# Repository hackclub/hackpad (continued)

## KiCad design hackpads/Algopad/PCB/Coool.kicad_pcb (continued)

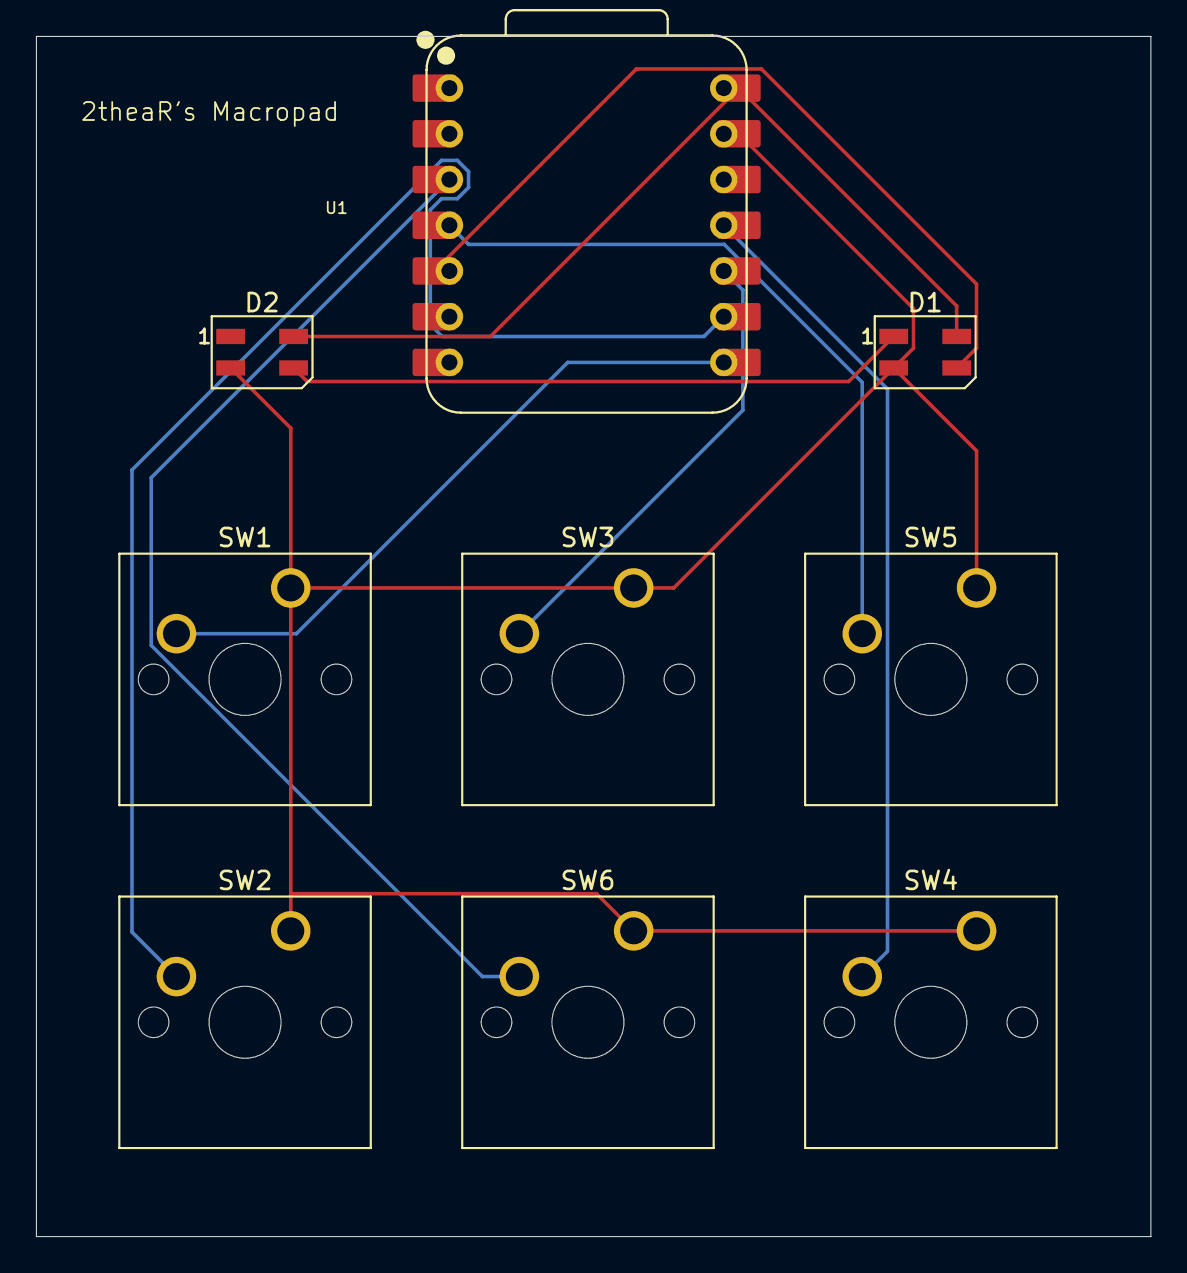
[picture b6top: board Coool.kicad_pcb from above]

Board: 2 copper layers, 61.9 x 66.7 mm, 9 parts (0 on the bottom side), 10 nets.
